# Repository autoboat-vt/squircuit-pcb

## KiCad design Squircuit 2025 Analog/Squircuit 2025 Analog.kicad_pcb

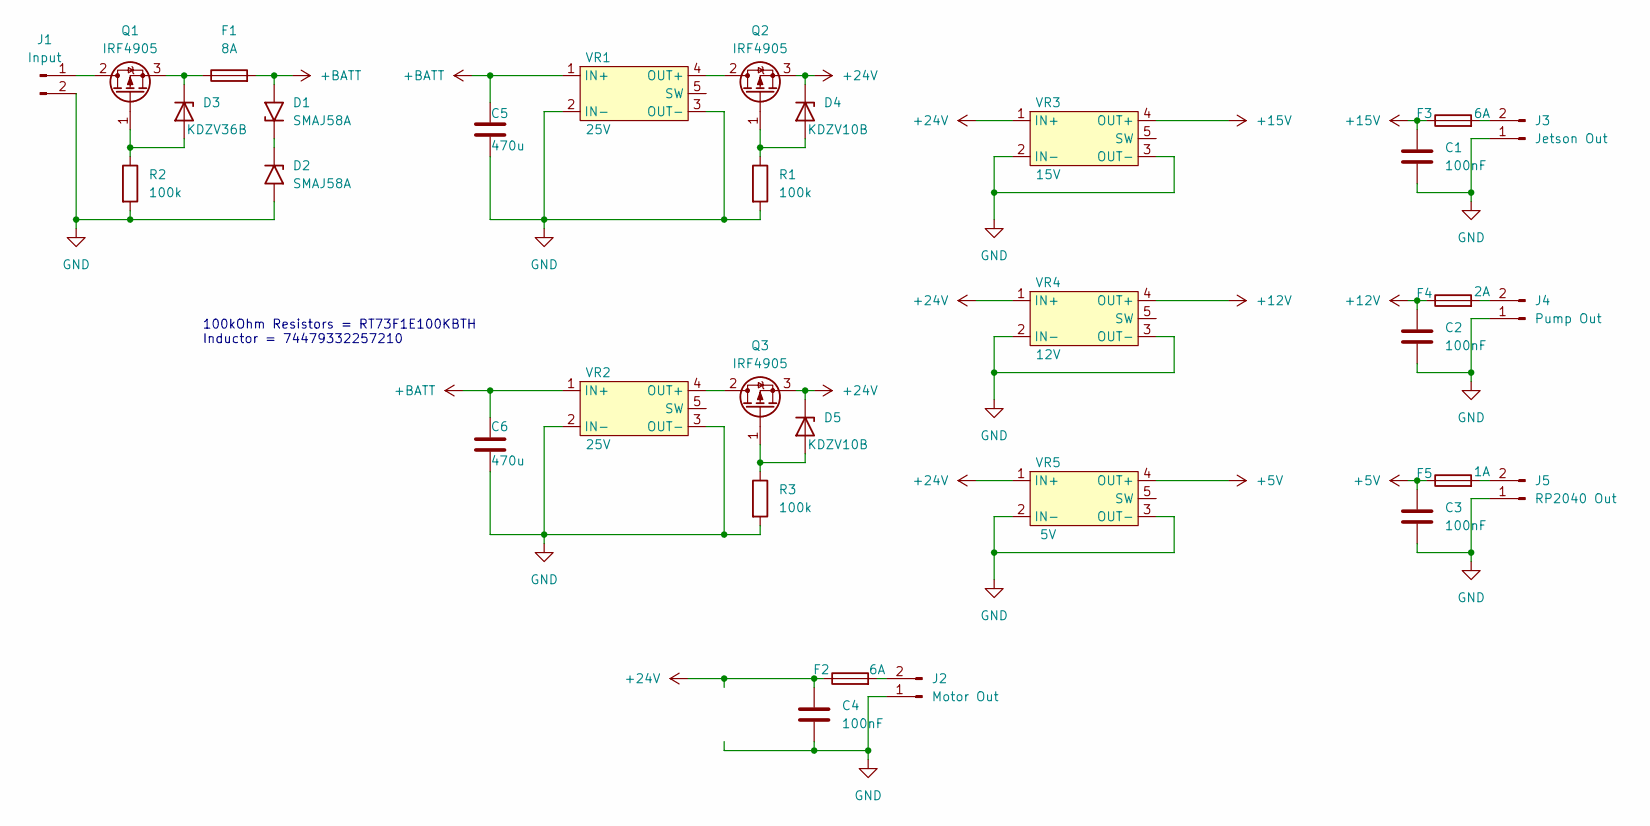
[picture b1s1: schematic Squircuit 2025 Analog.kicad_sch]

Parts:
C1, C2, C3, C4: 100nF; R_0805_2012Metric
C5, C6: 470u; CP_Elec_18x17.5
D1, D2: SMAJ58A; D_SMA
D3: KDZV36B; Vishay_SMPA
D4, D5: KDZV10B; Vishay_SMPA
F1: 8A; Fuseholder_Cylinder-5x20mm_Schurter_0031_8201_Horizontal_Op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
F2, F3: 6A; Fuseholder_Cylinder-5x20mm_Schurter_0031_8201_Horizontal_Op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
F4: 2A; Fuseholder_Cylinder-5x20mm_Schurter_0031_8201_Horizontal_Op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
F5: 1A; Fuseholder_Cylinder-5x20mm_Schurter_0031_8201_Horizontal_Op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
J1: Input; TerminalBlock_MaiXu_MX126-5.0-02P_1x02_P5.00mm
J2: Motor Out; TerminalBlock_MaiXu_MX126-5.0-02P_1x02_P5.00mm
J3: Jetson Out; TerminalBlock_MaiXu_MX126-5.0-02P_1x02_P5.00mm
J4: Pump Out; TerminalBlock_MaiXu_MX126-5.0-02P_1x02_P5.00mm
J5: RP2040 Out; TerminalBlock_MaiXu_MX126-5.0-02P_1x02_P5.00mm
Q1, Q2, Q3: IRF4905; TO-220-3_Vertical
R1, R2, R3: 100k; R_0805_2012Metric
VR1, VR2: 25V; Module_SMAKN_LM2596HV
VR3: 15V; Module_SMAKN_LM2596HV
VR4: 12V; Module_SMAKN_LM2596HV
VR5: 5V; Module_SMAKN_LM2596HV

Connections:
+5V: C3.1, F5.1, VR5.4 (OUT+)
+12V: C2.1, F4.1, VR4.4 (OUT+)
+15V: C1.1, F3.1, VR3.4 (OUT+)
+24V: C4.1, D4.1 (K), D5.1 (K), F2.1, Q2.3 (S), Q3.3 (S), VR3.1 (IN+), VR4.1 (IN+), VR5.1 (IN+)
+BATT: C5.1, C6.1, D1.2 (A2), F1.2, VR1.1 (IN+), VR2.1 (IN+)
GND: C1.2, C2.2, C3.2, C4.2, C5.2, C6.2, D2.2 (A2), J1.2, J2.1, J3.1, J4.1, J5.1, R1.2, R2.2, R3.2, VR1.2 (IN-), VR1.3 (OUT-), VR2.2 (IN-), VR2.3 (OUT-), VR3.2 (IN-), VR3.3 (OUT-), VR4.2 (IN-), VR4.3 (OUT-), VR5.2 (IN-), VR5.3 (OUT-)
unnamed: D1.1 (A1), D2.1 (A1)
unnamed: D3.2 (A), Q1.1 (G), R2.1
unnamed: D3.1 (K), F1.1, Q1.3 (S)
unnamed: D4.2 (A), Q2.1 (G), R1.1
unnamed: D5.2 (A), Q3.1 (G), R3.1
unnamed: J1.1, Q1.2 (D)
unnamed: F2.2, J2.2
unnamed: F3.2, J3.2
unnamed: F4.2, J4.2
unnamed: F5.2, J5.2
unnamed: Q2.2 (D), VR1.4 (OUT+)
unnamed: Q3.2 (D), VR2.4 (OUT+)

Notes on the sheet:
100kOhm Resistors = RT73F1E100KBTH Inductor = 74479332257210

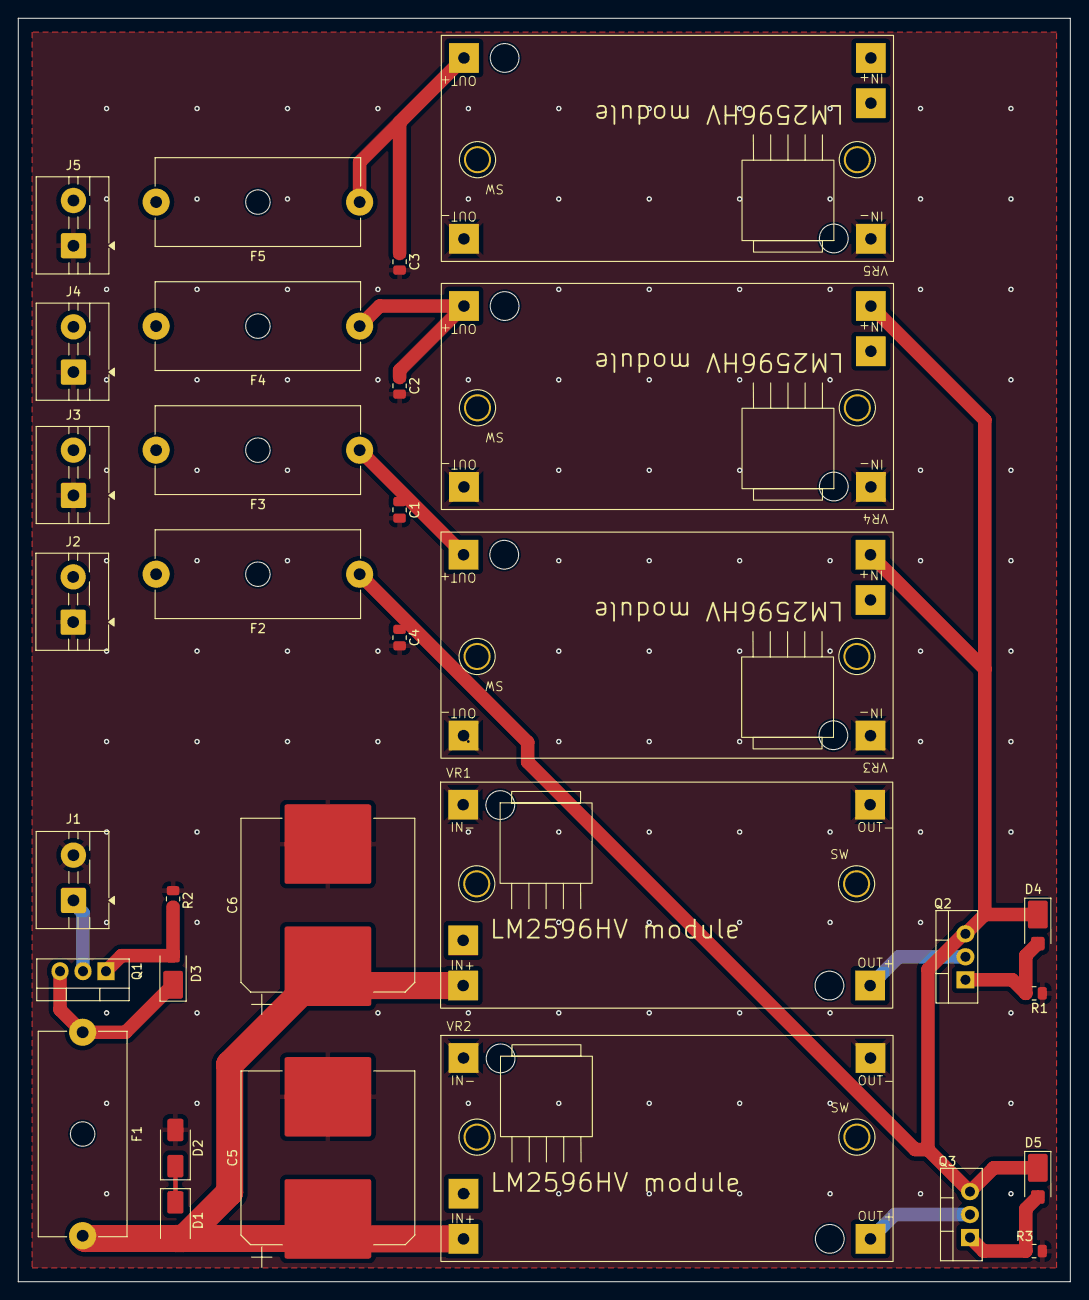
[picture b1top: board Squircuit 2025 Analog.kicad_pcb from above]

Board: 2 copper layers, 116.3 x 139.7 mm, 32 parts (0 on the bottom side), 18 nets.

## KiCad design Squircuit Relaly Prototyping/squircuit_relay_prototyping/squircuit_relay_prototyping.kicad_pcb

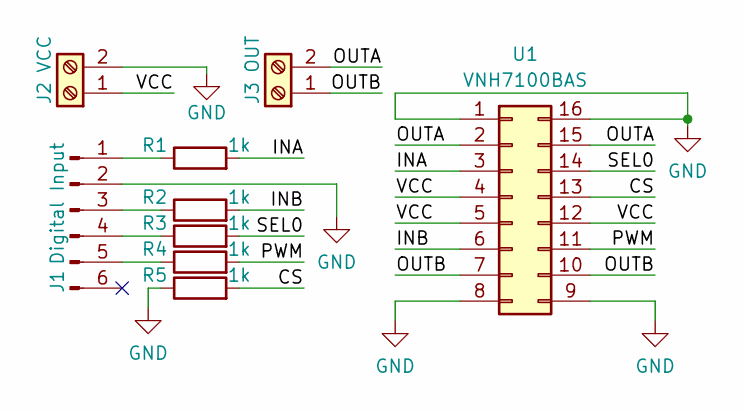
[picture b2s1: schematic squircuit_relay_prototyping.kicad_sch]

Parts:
J1: Digital Input; PinHeader_1x06_P2.54mm_Horizontal
J2: VCC; TerminalBlock_bornier-2_P5.08mm
J3: OUT; TerminalBlock_bornier-2_P5.08mm
R1, R2, R3, R4, R5: 1k; R_Axial_DIN0207_L6.3mm_D2.5mm_P10.16mm_Horizontal
U1: VNH7100BAS; SOIC-16_3.9x9.9mm_P1.27mm

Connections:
/CS: R5.2, U1.13
/INA: R1.2, U1.3
/INB: R2.2, U1.6
/OUTA: J3.2, U1.2, U1.15
/OUTB: J3.1, U1.7, U1.10
/PWM: R4.2, U1.11
/SEL0: R3.2, U1.14
/VCC: J2.1, U1.4, U1.5, U1.12
GND: J1.2, J2.2, R5.1, U1.1, U1.8, U1.9, U1.16
unnamed: J1.1, R1.1
unnamed: J1.3, R2.1
unnamed: J1.4, R3.1
unnamed: J1.5, R4.1

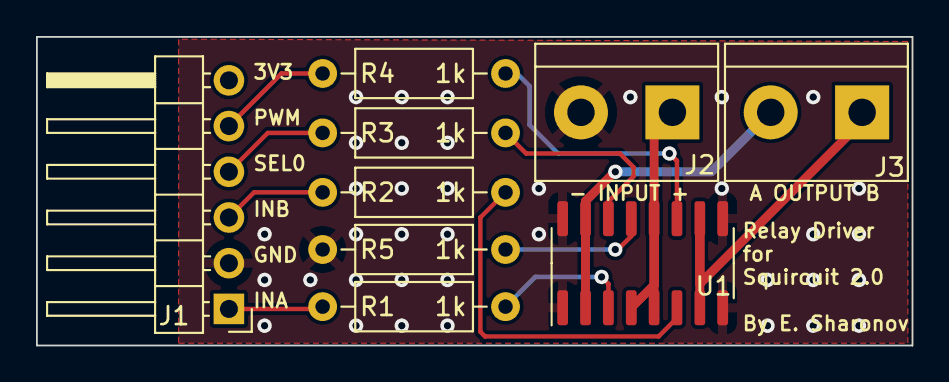
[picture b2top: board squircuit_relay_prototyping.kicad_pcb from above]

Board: 2 copper layers, 48.6 x 17.1 mm, 9 parts (0 on the bottom side), 13 nets.

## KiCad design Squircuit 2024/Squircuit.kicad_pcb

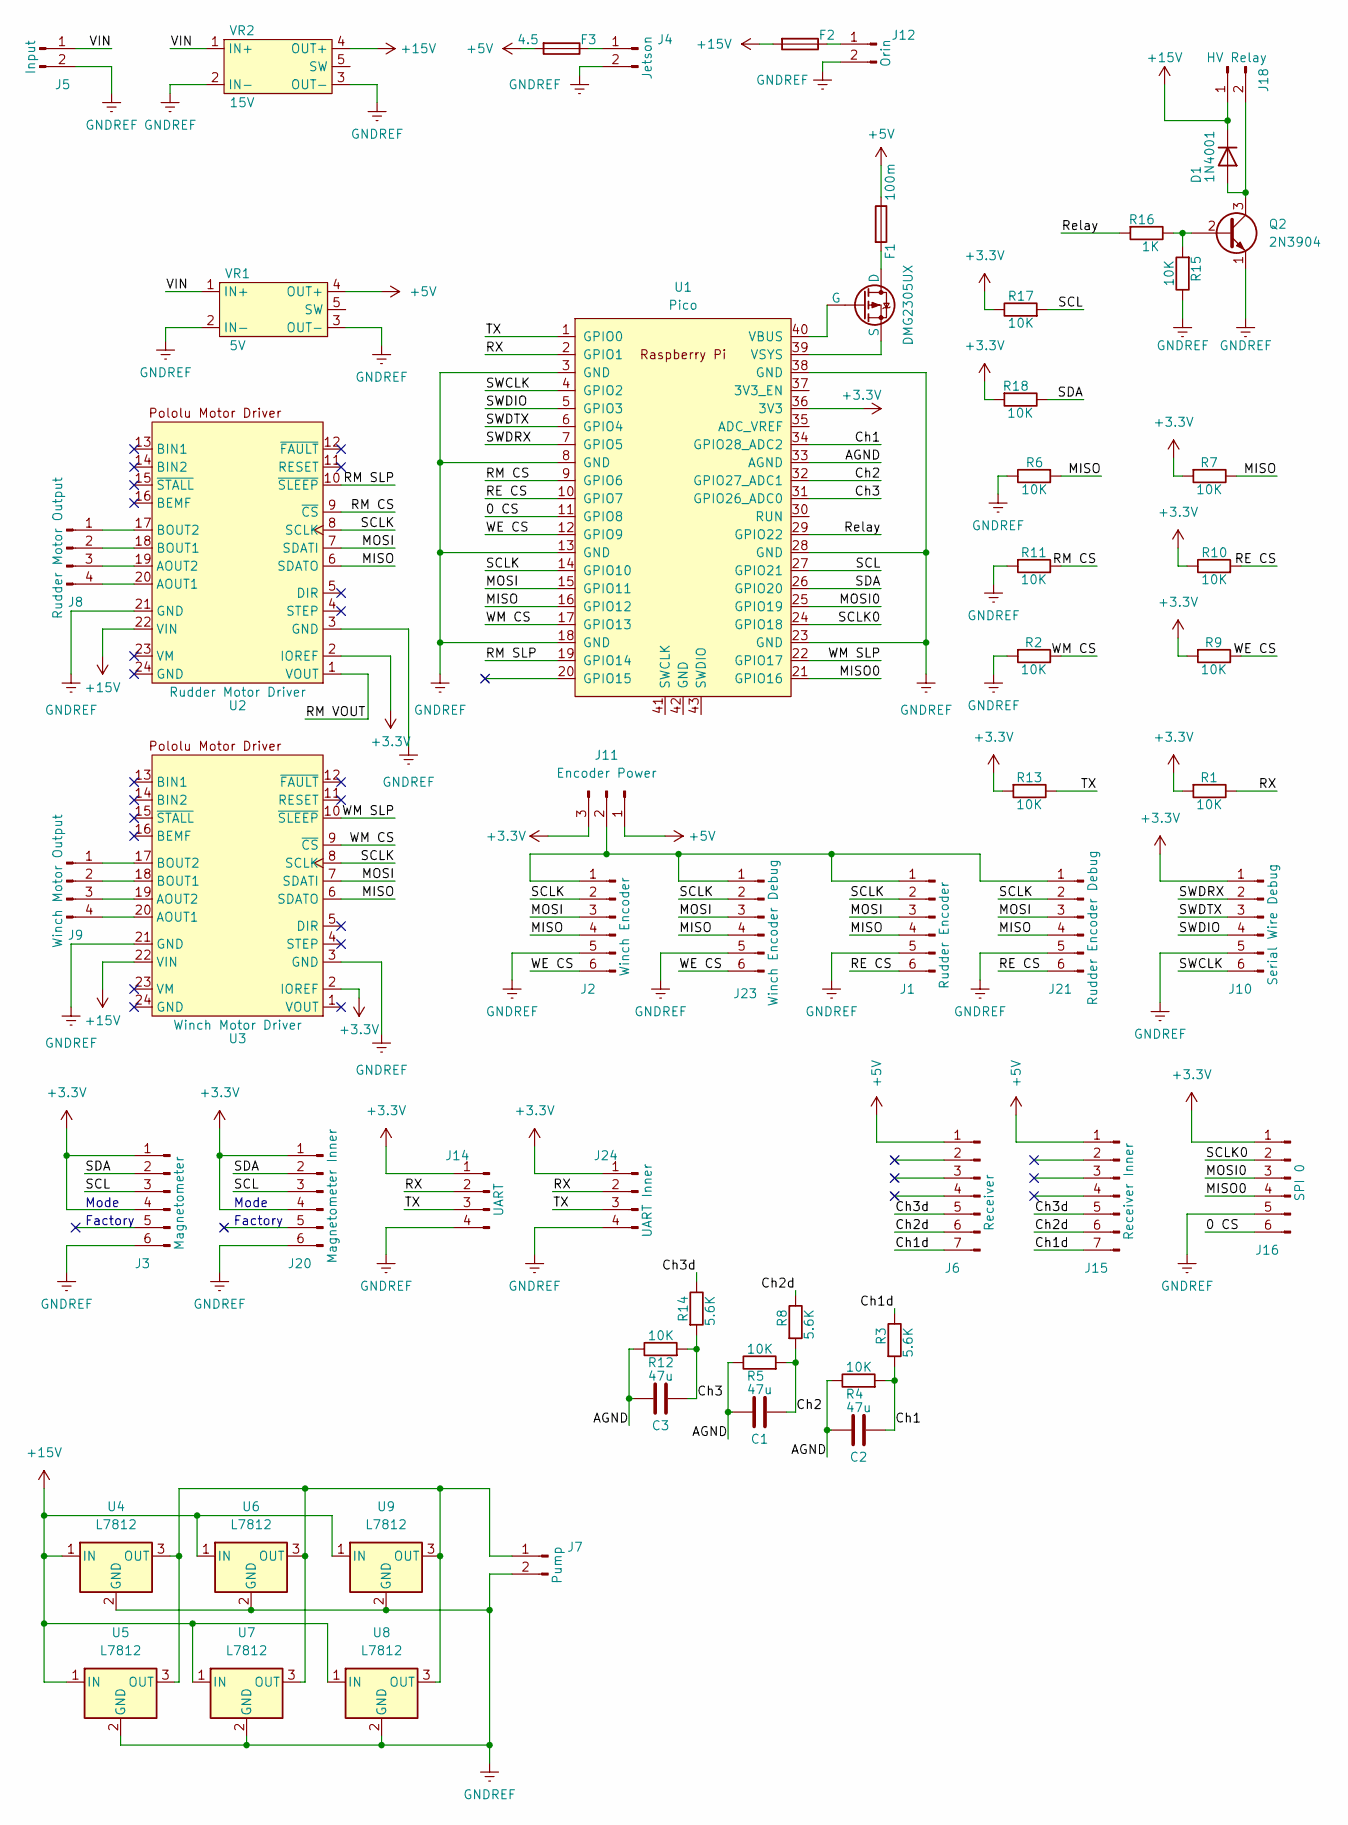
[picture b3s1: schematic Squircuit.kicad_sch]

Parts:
C1, C2, C3: 47u; CP_Radial_D6.3mm_P2.50mm
D1: 1N4001; D_DO-41_SOD81_P10.16mm_Horizontal
F1: 100m; Fuseholder_Cylinder-5x20mm_Stelvio-Kontek_PTF78_Horizontal_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
F2: Fuseholder_Cylinder-5x20mm_Stelvio-Kontek_PTF78_Horizontal_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
F3: 4.5; Fuseholder_Cylinder-5x20mm_Stelvio-Kontek_PTF78_Horizontal_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
J1: Rudder Encoder; JST_EH_S6B-EH_1x06_P2.50mm_Horizontal
J2: Winch Encoder; JST_EH_S6B-EH_1x06_P2.50mm_Horizontal
J3: Magnetometer; JST_EH_S6B-EH_1x06_P2.50mm_Horizontal
J4: Jetson; TerminalBlock_Phoenix_MKDS-1,5-2-5.08_1x02_P5.08mm_Horizont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
J5: Input; TerminalBlock_Phoenix_MKDS-1,5-2-5.08_1x02_P5.08mm_Horizont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
J6: Receiver; JST_EH_S7B-EH_1x07_P2.50mm_Horizontal
J7: Pump; TerminalBlock_Phoenix_MKDS-1,5-2-5.08_1x02_P5.08mm_Horizont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
J8: Rudder Motor Output; TerminalBlock_Phoenix_MKDS-1,5-4-5.08_1x04_P5.08mm_Horizont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
J9: Winch Motor Output; TerminalBlock_Phoenix_MKDS-1,5-4-5.08_1x04_P5.08mm_Horizont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
J10: Serial Wire Debug; PinHeader_1x06_P2.54mm_Vertical
J11: Encoder Power; PinHeader_1x03_P2.54mm_Vertical
J12: Orin; TerminalBlock_Phoenix_MKDS-1,5-2-5.08_1x02_P5.08mm_Horizont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
J14: UART; JST_EH_S4B-EH_1x04_P2.50mm_Horizontal
J15: Receiver Inner; PinHeader_1x07_P2.54mm_Vertical
J16: SPI 0; PinHeader_1x06_P2.54mm_Vertical
J18: HV Relay; TerminalBlock_Phoenix_MKDS-1,5-2-5.08_1x02_P5.08mm_Horizont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
J20: Magnetometer Inner; PinHeader_1x06_P2.54mm_Vertical
J21: Rudder Encoder Debug; PinHeader_1x06_P2.54mm_Vertical
J23: Winch Encoder Debug; PinHeader_1x06_P2.54mm_Vertical
J24: UART Inner; PinHeader_1x04_P2.54mm_Vertical
Q1: DMG2305UX; SOT-23
Q2: 2N3904; TO-92_Inline
R1, R2, R4, R5, R6, R7, R9, R10, R11, R12, R13, R15, R17, R18: 10K; R_Axial_DIN0207_L6.3mm_D2.5mm_P10.16mm_Horizontal
R3, R8, R14: 5.6K; R_Axial_DIN0207_L6.3mm_D2.5mm_P10.16mm_Horizontal
R16: 1K; R_Axial_DIN0207_L6.3mm_D2.5mm_P10.16mm_Horizontal
U1: Pico; RPi_Pico_SMD_TH
U2: Rudder Motor Driver; md38a
U3: Winch Motor Driver; md38a
U4, U5, U6, U7, U8, U9: L7812; TO-220-3_Vertical
VR1: 5V; VoltageReg_SMAKN
VR2: 15V; VoltageReg_SMAKN

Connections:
+3.3V: J3.1, J3.4, J10.1, J11.3, J14.1, J16.1, J20.1, J20.4, J24.1, R1.1, R7.1, R9.1, R10.2, R13.1, R17.2, R18.1, U1.36 (3V3), U2.2 (IOREF), U3.2 (IOREF)
+5V: F1.1, F3.2, J6.1, J11.1, J15.1, VR1.4 (OUT+)
+15V: D1.1 (K), F2.2, J18.1, U2.22 (VIN), U3.22 (VIN), U4.1 (IN), U5.1 (IN), U6.1 (IN), U7.1 (IN), U8.1 (IN), U9.1 (IN), VR2.4 (OUT+)
/0 CS: J16.6, U1.11 (GPIO8)
/AGND: C1.2, C2.2, C3.2, R4.2, R5.2, R12.2, U1.33 (AGND)
/Ch1: C2.1, R3.1, R4.1, U1.34 (GPIO28_ADC2)
/Ch1d: J6.7, J15.7, R3.2
/Ch2: C1.1, R5.1, R8.1, U1.32 (GPIO27_ADC1)
/Ch2d: J6.6, J15.6, R8.2
/Ch3: C3.1, R12.1, R14.1, U1.31 (GPIO26_ADC0)
/Ch3d: J6.5, J15.5, R14.2
/MISO: J1.4, J2.4, J21.4, J23.4, R6.1, R7.2, U1.16 (GPIO12), U2.6 (SDATO), U3.6 (SDATO)
/MISO0: J16.4, U1.21 (GPIO16)
/MOSI: J1.3, J2.3, J21.3, J23.3, U1.15 (GPIO11), U2.7 (SDATI), U3.7 (SDATI)
/MOSI0: J16.3, U1.25 (GPIO19)
/RE CS: J1.6, J21.6, R10.1, U1.10 (GPIO7)
/RM CS: R11.2, U1.9 (GPIO6), U2.9 (~CS)
/RM VOUT: U2.1 (VOUT)
/RX: J14.2, J24.2, R1.2, U1.2 (GPIO1)
/Relay: R16.1, U1.29 (GPIO22)
/RМ SLP: U1.19 (GPIO14), U2.10 (~SLEEP)
/SCL: J3.3, J20.3, R17.1, U1.27 (GPIO21)
/SCLK: J1.2, J2.2, J21.2, J23.2, U1.14 (GPIO10), U2.8 (SCLK), U3.8 (SCLK)
/SCLK0: J16.2, U1.24 (GPIO18)
/SDA: J3.2, J20.2, R18.2, U1.26 (GPIO20)
/SWCLK: J10.6, U1.4 (GPIO2)
/SWDIO: J10.4, U1.5 (GPIO3)
/SWDRX: J10.2, U1.7 (GPIO5)
/SWDTX: J10.3, U1.6 (GPIO4)
/TX: J14.3, J24.3, R13.2, U1.1 (GPIO0)
/VIN: J5.1, VR1.1 (IN+), VR2.1 (IN+)
/WE CS: J2.6, J23.6, R9.2, U1.12 (GPIO9)
/WM CS: R2.2, U1.17 (GPIO13), U3.9 (~CS)
/WM SLP: U1.22 (GPIO17), U3.10 (~SLEEP)
GNDREF: J1.5, J2.5, J3.6, J4.2, J5.2, J7.2, J10.5, J12.2, J14.4, J16.5, J20.6, J21.5, J23.5, J24.4, Q2.1 (E), R2.1, R6.2, R11.1, R15.2, U1.3 (GND), U1.8 (GND), U1.13 (GND), U1.18 (GND), U1.23 (GND), U1.28 (GND), U1.38 (GND), U2.3 (GND), U2.21 (GND), U3.3 (GND), U3.21 (GND), U4.2 (GND), U5.2 (GND), U6.2 (GND), U7.2 (GND), U8.2 (GND), U9.2 (GND), VR1.2 (IN-), VR1.3 (OUT-), VR2.2 (IN-), VR2.3 (OUT-)
unnamed: D1.2 (A), J18.2, Q2.3 (C)
unnamed: J1.1, J2.1, J11.2, J21.1, J23.1
unnamed: F3.1, J4.1
unnamed: J7.1, U4.3 (OUT), U5.3 (OUT), U6.3 (OUT), U7.3 (OUT), U8.3 (OUT), U9.3 (OUT)
unnamed: J8.1, U2.17 (BOUT2)
unnamed: J8.2, U2.18 (BOUT1)
unnamed: J8.3, U2.19 (AOUT2)
unnamed: J8.4, U2.20 (AOUT1)
unnamed: J9.1, U3.17 (BOUT2)
unnamed: J9.2, U3.18 (BOUT1)
unnamed: J9.3, U3.19 (AOUT2)
unnamed: J9.4, U3.20 (AOUT1)
unnamed: F2.1, J12.1
unnamed: F1.2, Q1.1 (D)
unnamed: Q1.2 (G), U1.40 (VBUS)
unnamed: Q1.3 (S), U1.39 (VSYS)
unnamed: Q2.2 (B), R15.1, R16.2

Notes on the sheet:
Mode
Factory

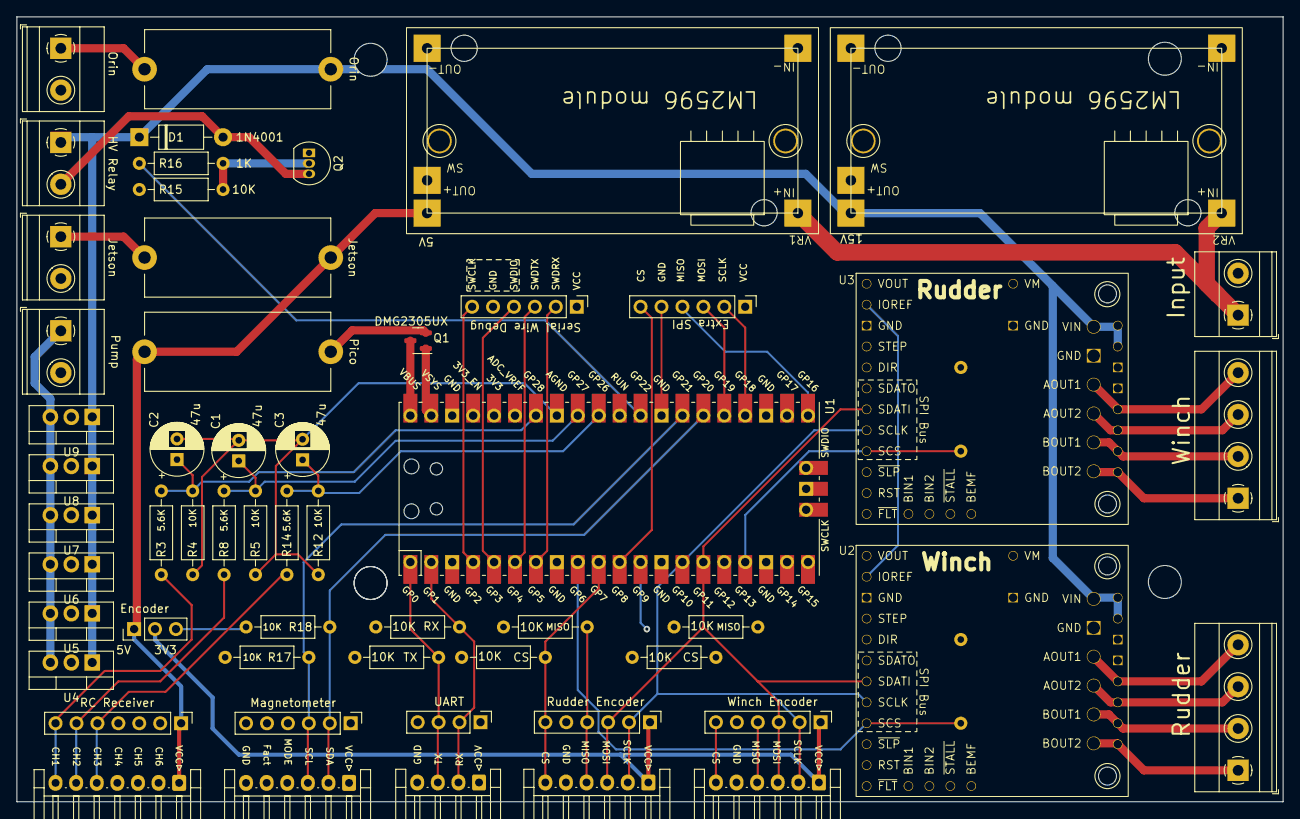
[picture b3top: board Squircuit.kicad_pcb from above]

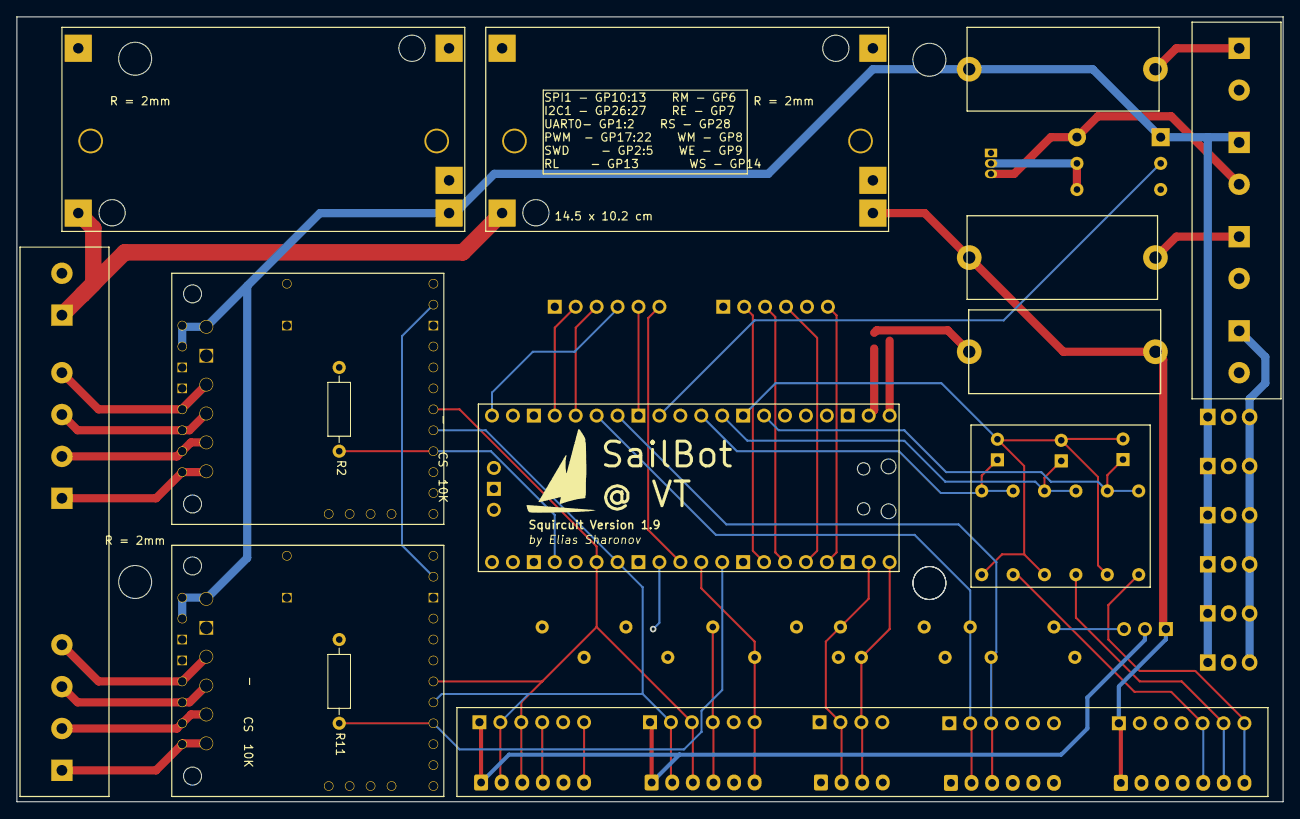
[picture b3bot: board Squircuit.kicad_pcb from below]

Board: 4 copper layers, 153.7 x 95.2 mm, 58 parts (2 on the bottom side), 51 nets.

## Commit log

2024-12-28 Reorganized
2025-02-01 Added the relay driver module
2025-03-04 added todo
2025-03-04 NOT COOL ELIAS. NOT COOL.
2025-03-04 updated todo list
2025-03-04 updated todo list 2
2025-09-03 Lets see if this will work
2025-09-05 Added the power PCB prototype (Buck convnerter dimensions to be corrected)
2025-09-06 All of the components are on the PCB
2025-09-06 (symbol "GNDREF_2" (power) (pin_numbers (hide yes) ) (pin_names (offset 0) (hide yes) ) (exclude_from_sim no) (in_bom yes) (on_board yes) (property "Reference" "#PWR" (at 0 -6.35 0) (effects (font (s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
2025-09-19 Hopefully this works -- Schematic for review.
2025-09-19 test
